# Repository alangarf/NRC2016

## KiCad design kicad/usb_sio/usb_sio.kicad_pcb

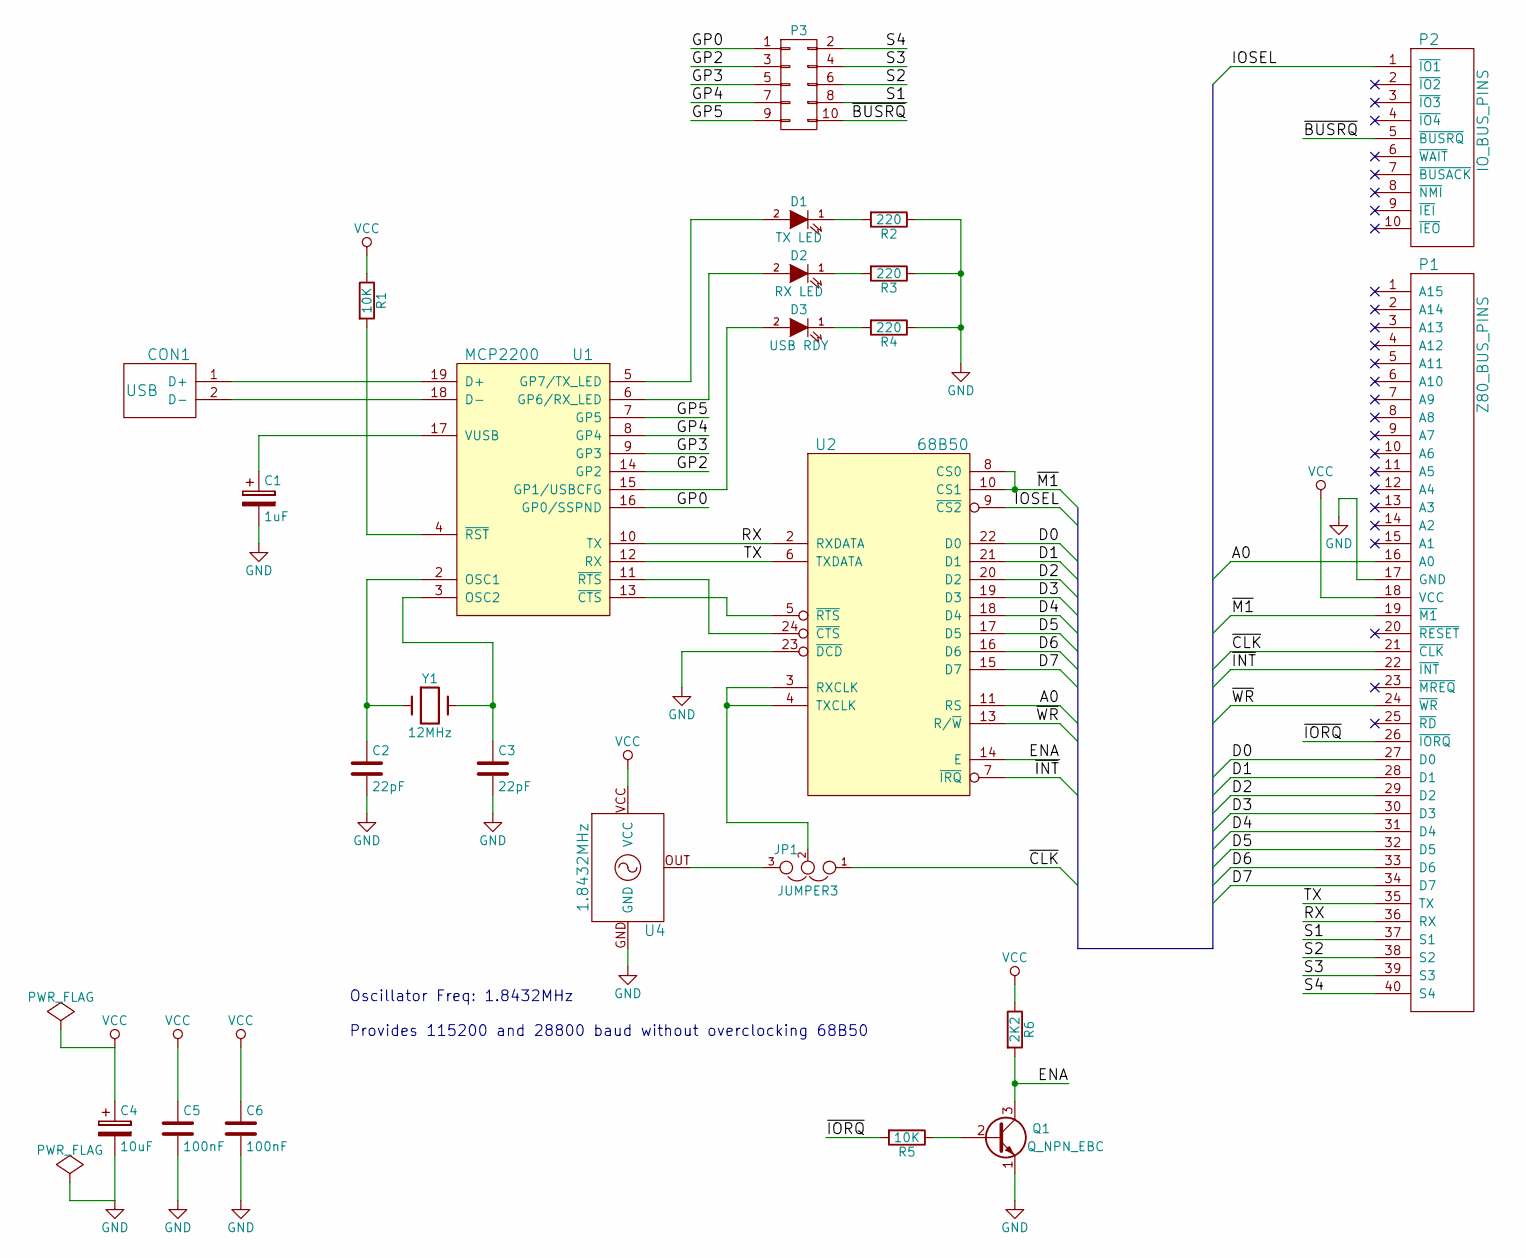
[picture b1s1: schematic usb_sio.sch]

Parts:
C1: 1uF; C_Radial_D5_L6_P2.5
C2, C3: 22pF; C_Disc_D3_P2.5
C4: 10uF; C_Radial_D6.3_L11.2_P2.5
C5, C6: 100nF; C_Disc_D3_P2.5
CON1: USB; Pin_Header_Angled_1x02_nrc2016
D1: TX LED; LED-5MM
D2: RX LED; LED-5MM
D3: USB RDY; LED-5MM
JP1: JUMPER3; Pin_Header_Straight_1x03
P1: Z80_BUS_PINS; Pin_Header_Angled_1x40_nrc2016
P2: IO_BUS_PINS; Pin_Header_Angled_1x10_nrc2016
P3: CONN_02X05; Pin_Header_Straight_2x05
Q1: Q_NPN_EBC; TO-92_Molded_Narrow
R1, R5: 10K; Resistor_Horizontal_RM10mm
R2, R3, R4: 220; Resistor_Horizontal_RM10mm
R6: 2K2; Resistor_Horizontal_RM10mm
U1: MCP2200; SOIC-20W_7.5x12.8mm_Pitch1.27mm
U2: 68B50; DIP-24_W15.24mm_LongPads
U4: 1.8432MHz; OSC_MULTIPACKAGE_DIP
Y1: 12MHz; Crystal_HC49-U_Vertical

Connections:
/A0: P1.16 (A0), U2.11 (RS)
/D0: P1.27 (D0), U2.22 (D0)
/D1: P1.28 (D1), U2.21 (D1)
/D2: P1.29 (D2), U2.20 (D2)
/D3: P1.30 (D3), U2.19 (D3)
/D4: P1.31 (D4), U2.18 (D4)
/D5: P1.32 (D5), U2.17 (D5)
/D6: P1.33 (D6), U2.16 (D6)
/D7: P1.34 (D7), U2.15 (D7)
/ENA: Q1.3 (C), R6.2, U2.14 (E)
/GP0: P3.1, U1.16 (GP0/SSPND)
/GP2: P3.3, U1.14 (GP2)
/GP3: P3.5, U1.9 (GP3)
/GP4: P3.7, U1.8 (GP4)
/GP5: P3.9, U1.7 (GP5)
/RX: P1.36 (RX), U1.10 (TX), U2.2 (RXDATA)
/S1: P1.37 (S1), P3.8
/S2: P1.38 (S2), P3.6
/S3: P1.39 (S3), P3.4
/S4: P1.40 (S4), P3.2
/TX: P1.35 (TX), U1.12 (RX), U2.6 (TXDATA)
/~BUSRQ: P2.5 (~BUSRQ), P3.10
/~CLK: JP1.1, P1.21 (~CLK)
/~INT: P1.22 (~INT), U2.7 (~IRQ)
/~IORQ: P1.26 (~IORQ), R5.2
/~WR: P1.24 (~WR), U2.13 (R/~W)
GND: C1.2, C2.2, C3.2, C4.2, C5.2, C6.2, P1.17 (GND), Q1.1 (E), R2.1, R3.1, R4.1, U1.20 (GND), U2.1 (GND), U2.23 (~DCD), U4.GND
unnamed: C1.1, U1.17 (VUSB)
unnamed: C2.1, U1.2 (OSC1), Y1.1
unnamed: C3.1, U1.3 (OSC2), Y1.2
unnamed: CON1.1 (D+), U1.19 (D+)
unnamed: CON1.2 (D-), U1.18 (D-)
unnamed: D1.1 (K), R2.2
unnamed: D1.2 (A), U1.5 (GP7/TX_LED)
unnamed: D2.1 (K), R3.2
unnamed: D2.2 (A), U1.6 (GP6/RX_LED)
unnamed: D3.1 (K), R4.2
unnamed: D3.2 (A), U1.15 (GP1/USBCFG)
unnamed: JP1.2, U2.3 (RXCLK), U2.4 (TXCLK)
unnamed: JP1.3, U4.OUT
unnamed 40: P2.2 (~IO2); also elsewhere on the board
unnamed 41: P2.3 (~IO3); also elsewhere on the board
unnamed 42: P2.4 (~IO4); also elsewhere on the board
unnamed: Q1.2 (B), R5.1
unnamed: R1.2, U1.4 (~RST)
unnamed: U1.11 (~RTS), U2.24 (~CTS)
unnamed: U1.13 (~CTS), U2.5 (~RTS)

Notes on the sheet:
Oscillator Freq: 1.8432MHz Provides 115200 and 28800 baud without overclocking 68B50

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
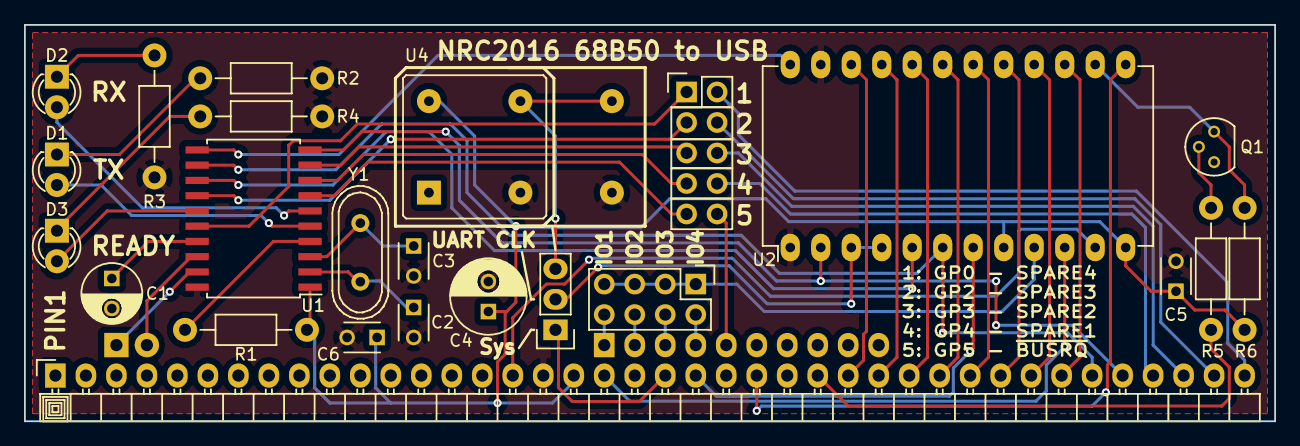
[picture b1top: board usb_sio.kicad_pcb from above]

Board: 2 copper layers, 104.1 x 33.0 mm, 27 parts (0 on the bottom side), 51 nets.

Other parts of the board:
LOGO1: BackLogo; nrc2016_top_logo_1600
P4: CONN_02X04; Pin_Header_Straight_2x04

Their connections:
unnamed 40: P4.6; also elsewhere on the board
unnamed 41: P4.4; also elsewhere on the board
unnamed 42: P4.2; also elsewhere on the board

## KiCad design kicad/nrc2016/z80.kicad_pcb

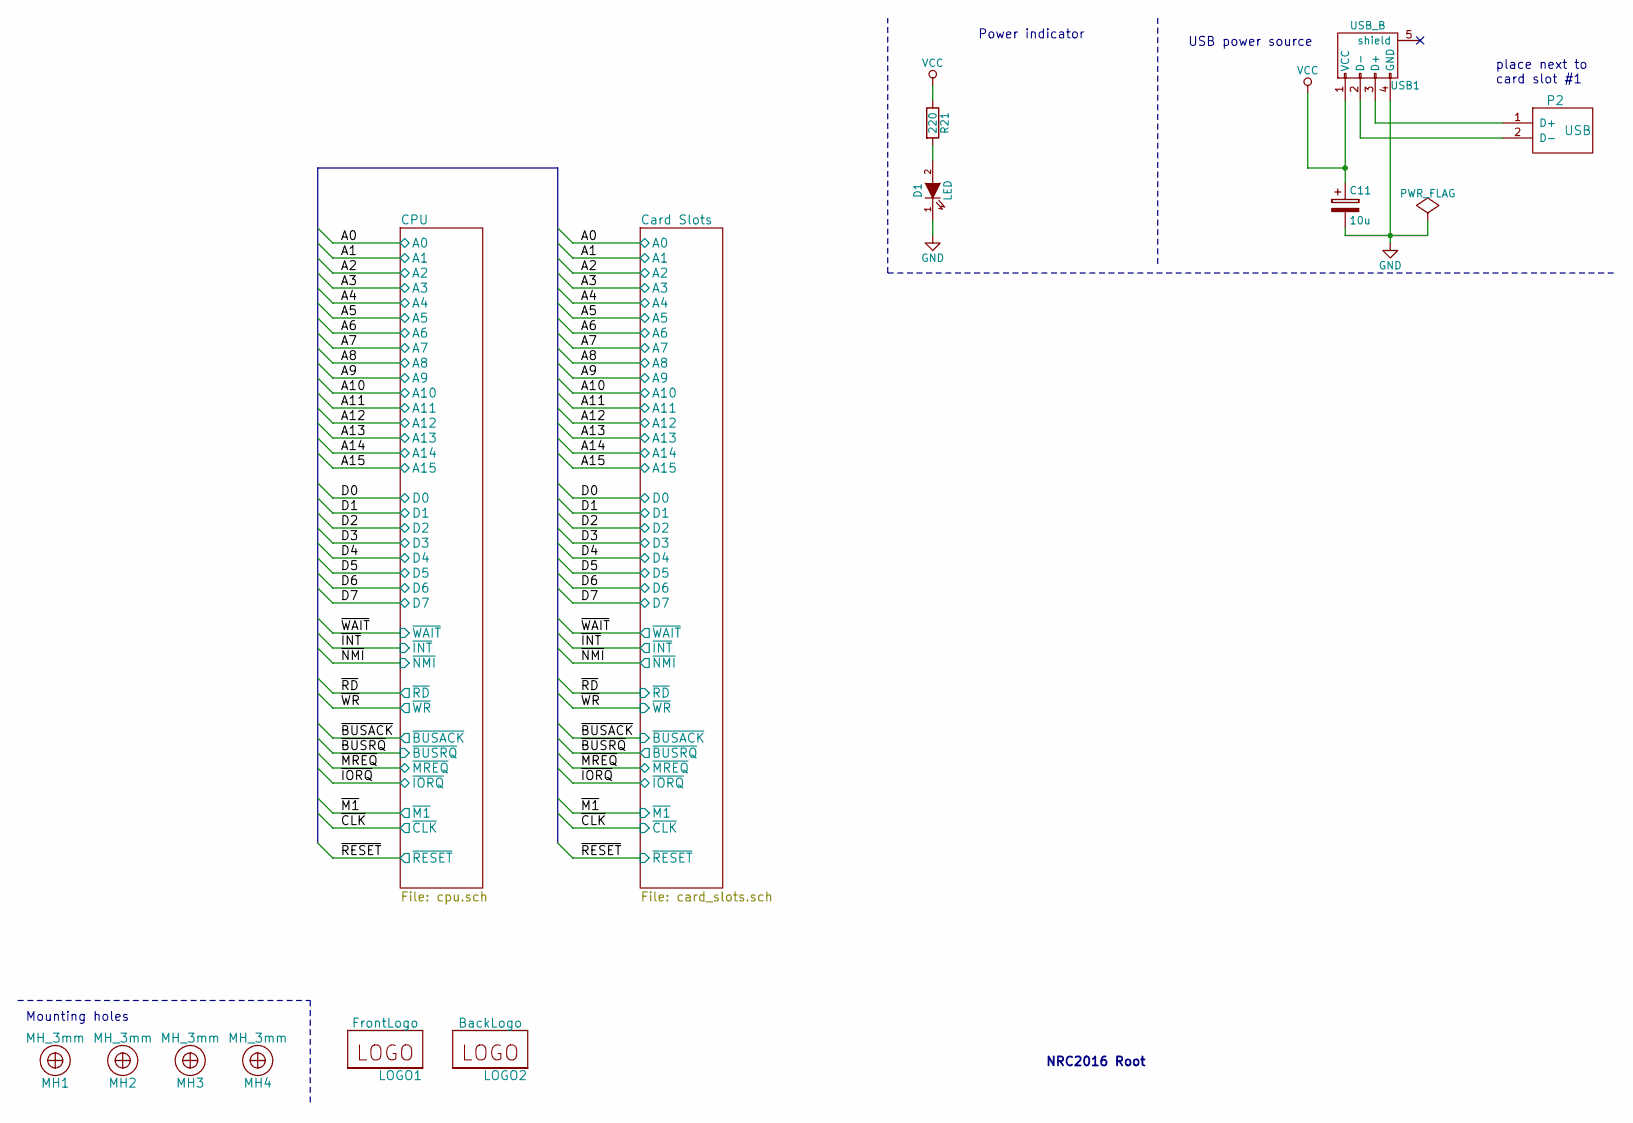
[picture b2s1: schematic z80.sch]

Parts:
C11: 10u; C_Radial_D6.3_L11.2_P2.5
D1: LED; LED-3MM
LOGO1: FrontLogo; nrc2016_top_logo_1600
LOGO2: BackLogo; nrc2016_bottom_logo_600_v2
MH1, MH2, MH3, MH4: MH_3mm; MountingHole_3.2mm_M3
P2: USB; Socket_Strip_Straight_1x02
R21: 220; Resistor_Horizontal_RM7mm
USB1: USB_B

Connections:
GND: C11.2, D1.1 (K), USB1.4 (GND); also elsewhere on the board
unnamed: D1.2 (A), R21.2
unnamed: P2.1 (D+), USB1.3 (D+)
unnamed: P2.2 (D-), USB1.2 (D-)

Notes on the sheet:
NRC2016 Root
Mounting holes
USB power source
Power indicator
place next to card slot #1

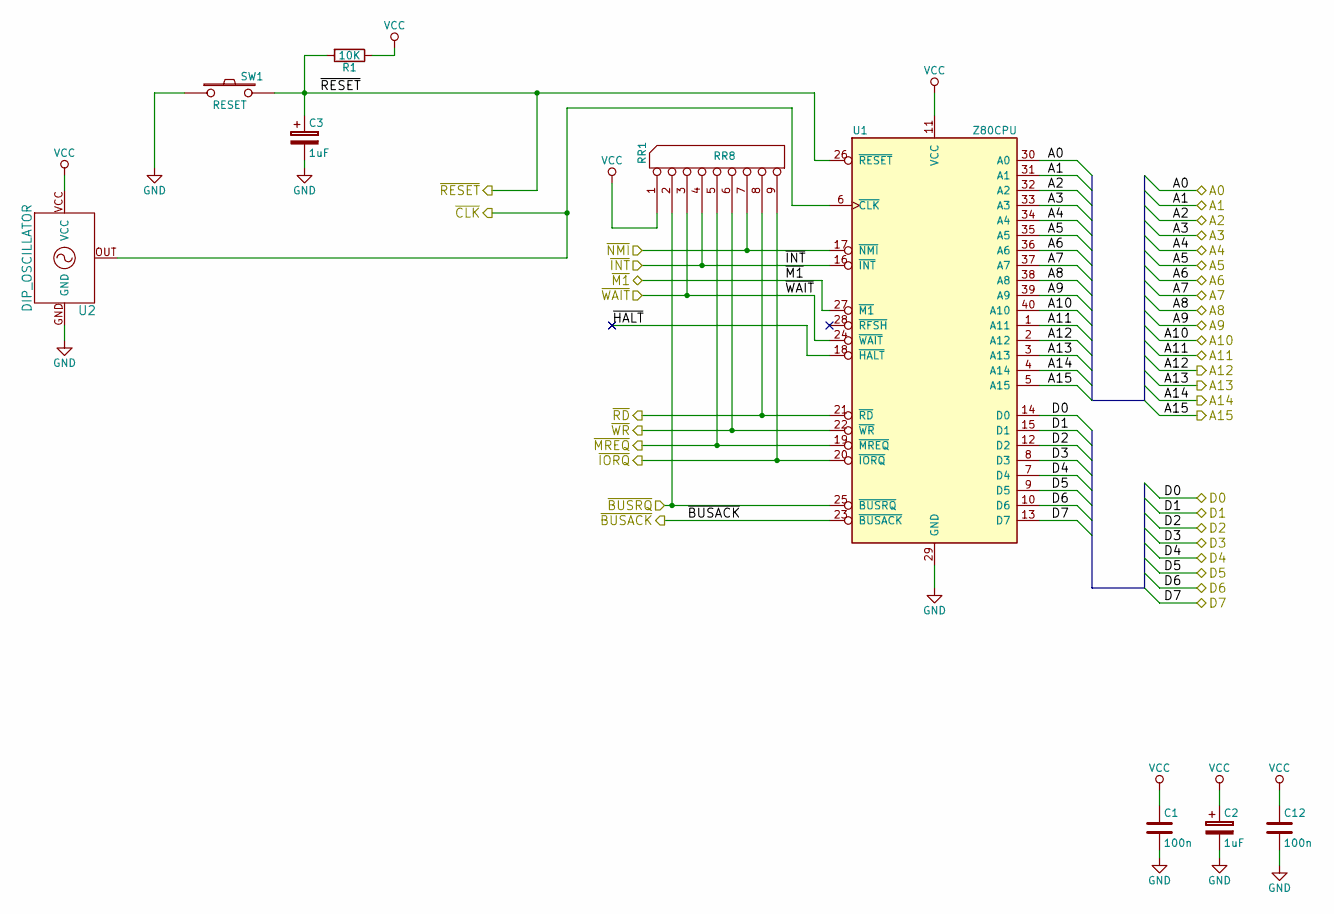
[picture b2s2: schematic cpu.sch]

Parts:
C1, C12: 100n; C_Rect_L4_W2.5_P2.5
C2, C3: 1uF; C_Radial_D5_L6_P2.5
R1: 10K; Resistor_Horizontal_RM7mm
RR1: RR8; Resistor_Array_SIP8
SW1: RESET; SW_PUSH_SMALL
U1: Z80CPU; DIP-40_W15.24mm_LongPads
U2: DIP_OSCILLATOR; OSC_MULTIPACKAGE_DIP

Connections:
/A0: U1.30 (A0); also elsewhere on the board
/A1: U1.31 (A1); also elsewhere on the board
/A2: U1.32 (A2); also elsewhere on the board
/A3: U1.33 (A3); also elsewhere on the board
/A4: U1.34 (A4); also elsewhere on the board
/A5: U1.35 (A5); also elsewhere on the board
/A6: U1.36 (A6); also elsewhere on the board
/A7: U1.37 (A7); also elsewhere on the board
/A8: U1.38 (A8); also elsewhere on the board
/A9: U1.39 (A9); also elsewhere on the board
/A10: U1.40 (A10); also elsewhere on the board
/A11: U1.1 (A11); also elsewhere on the board
/A12: U1.2 (A12); also elsewhere on the board
/A13: U1.3 (A13); also elsewhere on the board
/A14: U1.4 (A14); also elsewhere on the board
/A15: U1.5 (A15); also elsewhere on the board
/D0: U1.14 (D0); also elsewhere on the board
/D1: U1.15 (D1); also elsewhere on the board
/D2: U1.12 (D2); also elsewhere on the board
/D3: U1.8 (D3); also elsewhere on the board
/D4: U1.7 (D4); also elsewhere on the board
/D5: U1.9 (D5); also elsewhere on the board
/D6: U1.10 (D6); also elsewhere on the board
/D7: U1.13 (D7); also elsewhere on the board
/~BUSACK: U1.23 (~BUSACK~); also elsewhere on the board
/~BUSRQ: RR1.2, U1.25 (~BUSRQ~); also elsewhere on the board
/~CLK: U1.6 (~CLK~), U2.OUT; also elsewhere on the board
/~INT: RR1.4, U1.16 (~INT~); also elsewhere on the board
/~IORQ: RR1.9, U1.20 (~IORQ~); also elsewhere on the board
/~M1: U1.27 (~M1~); also elsewhere on the board
/~MREQ: RR1.5, U1.19 (~MREQ~); also elsewhere on the board
/~NMI: RR1.7, U1.17 (~NMI~); also elsewhere on the board
/~RD: RR1.8, U1.21 (~RD~); also elsewhere on the board
/~WAIT: RR1.3, U1.24 (~WAIT~); also elsewhere on the board
/~WR: RR1.6, U1.22 (~WR~); also elsewhere on the board
GND: C1.2, C2.2, C3.2, C12.2, SW1.1, U1.29 (GND), U2.GND; also elsewhere on the board

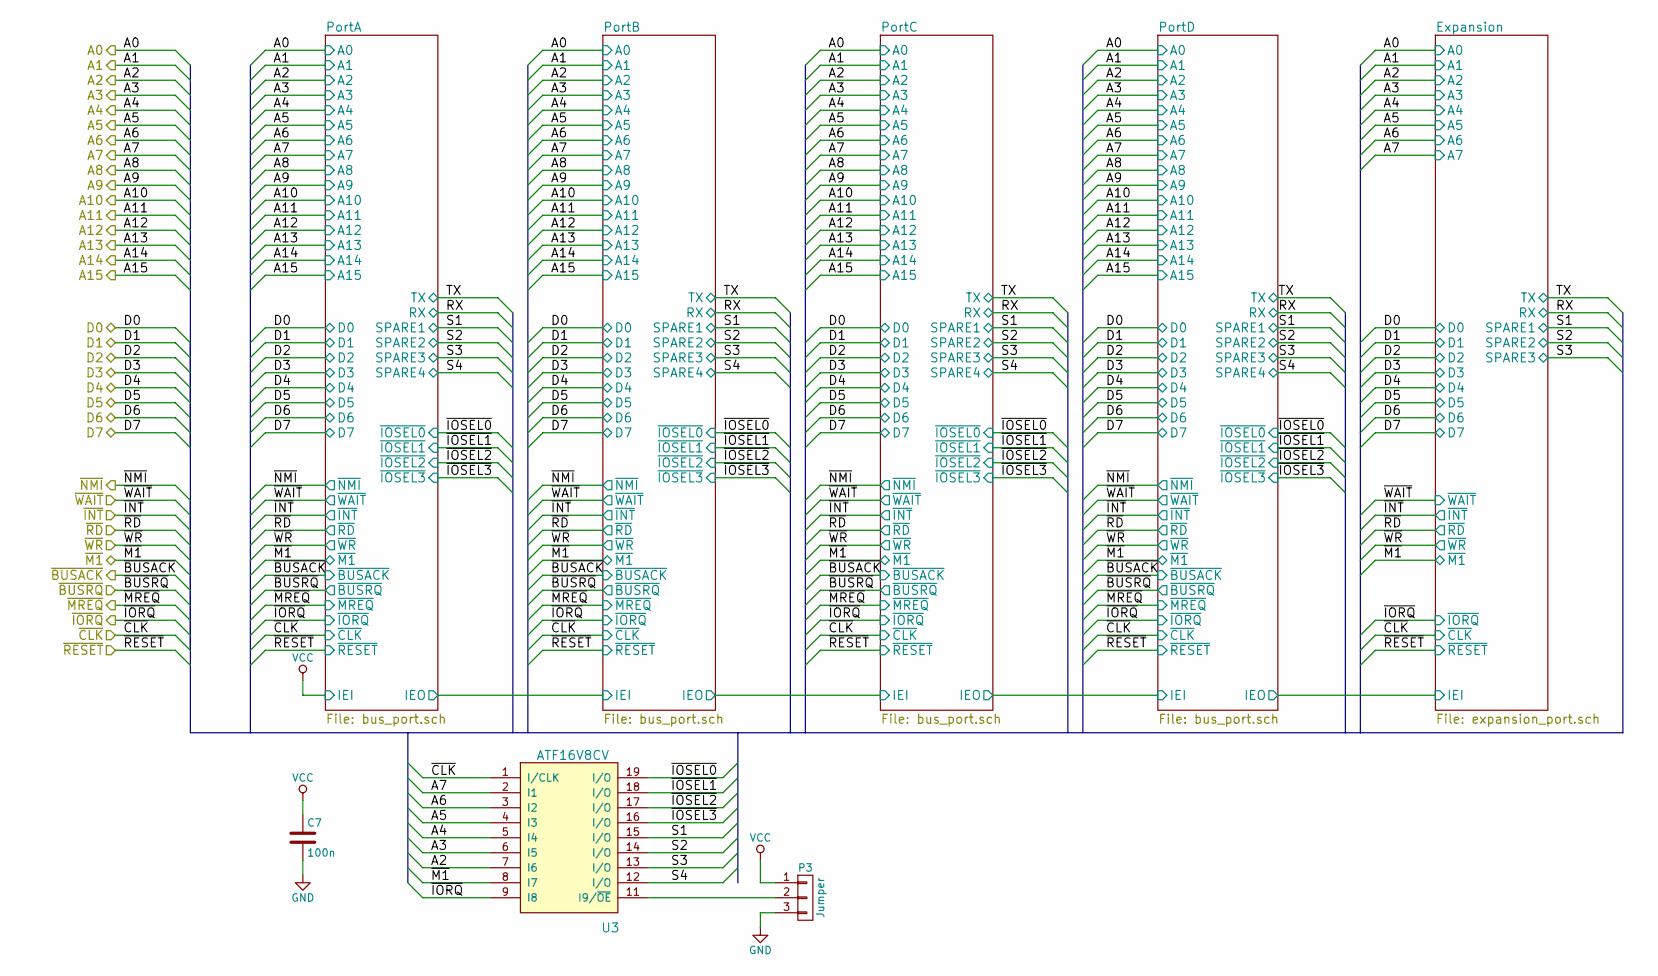
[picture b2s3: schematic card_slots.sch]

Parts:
C7: 100n; C_Rect_L4_W2.5_P2.5
P3: Jumper; Pin_Header_Straight_1x03
U3: ATF16V8CV; DIP-20_W7.62mm_LongPads

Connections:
/A2: U3.7 (I6); also elsewhere on the board
/A3: U3.6 (I5); also elsewhere on the board
/A4: U3.5 (I4); also elsewhere on the board
/A5: U3.4 (I3); also elsewhere on the board
/A6: U3.3 (I2); also elsewhere on the board
/A7: U3.2 (I1); also elsewhere on the board
/Card Slots/S1: U3.15 (I/O); also elsewhere on the board
/Card Slots/S2: U3.14 (I/O); also elsewhere on the board
/Card Slots/S3: U3.13 (I/O); also elsewhere on the board
/Card Slots/S4: U3.12 (I/O); also elsewhere on the board
/Card Slots/~IOSEL0: U3.19 (I/O); also elsewhere on the board
/Card Slots/~IOSEL1: U3.18 (I/O); also elsewhere on the board
/Card Slots/~IOSEL2: U3.17 (I/O); also elsewhere on the board
/Card Slots/~IOSEL3: U3.16 (I/O); also elsewhere on the board
/~CLK: U3.1 (I/CLK); also elsewhere on the board
/~IORQ: U3.9 (I8); also elsewhere on the board
/~M1: U3.8 (I7); also elsewhere on the board
GND: C7.2, P3.3, U3.10 (GND); also elsewhere on the board
unnamed: P3.2, U3.11 (I9/~OE)

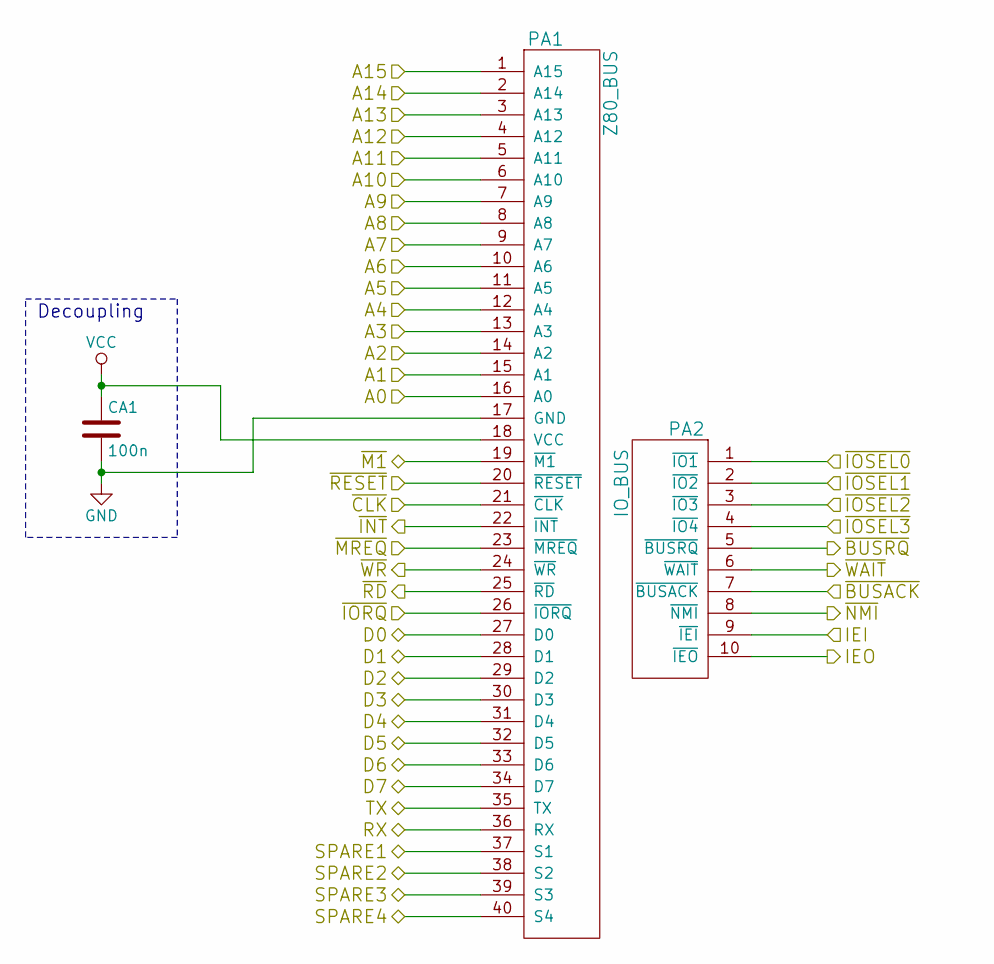
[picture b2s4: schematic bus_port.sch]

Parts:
CA1: 100n; C_Rect_L4_W2.5_P2.5
PA1: Z80_BUS; Socket_Strip_Straight_1x40
PA2: IO_BUS; Socket_Strip_Straight_1x10_NRC2016

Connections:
/A0: PA1.16 (A0); also elsewhere on the board
/A1: PA1.15 (A1); also elsewhere on the board
/A2: PA1.14 (A2); also elsewhere on the board
/A3: PA1.13 (A3); also elsewhere on the board
/A4: PA1.12 (A4); also elsewhere on the board
/A5: PA1.11 (A5); also elsewhere on the board
/A6: PA1.10 (A6); also elsewhere on the board
/A7: PA1.9 (A7); also elsewhere on the board
/A8: PA1.8 (A8); also elsewhere on the board
/A9: PA1.7 (A9); also elsewhere on the board
/A10: PA1.6 (A10); also elsewhere on the board
/A11: PA1.5 (A11); also elsewhere on the board
/A12: PA1.4 (A12); also elsewhere on the board
/A13: PA1.3 (A13); also elsewhere on the board
/A14: PA1.2 (A14); also elsewhere on the board
/A15: PA1.1 (A15); also elsewhere on the board
/Card Slots/PortB/IEI: PA2.10 (~IEO); also elsewhere on the board
/Card Slots/RX: PA1.36 (RX); also elsewhere on the board
/Card Slots/S1: PA1.37 (S1); also elsewhere on the board
/Card Slots/S2: PA1.38 (S2); also elsewhere on the board
/Card Slots/S3: PA1.39 (S3); also elsewhere on the board
/Card Slots/S4: PA1.40 (S4); also elsewhere on the board
/Card Slots/TX: PA1.35 (TX); also elsewhere on the board
/Card Slots/~IOSEL0: PA2.1 (~IO1); also elsewhere on the board
/Card Slots/~IOSEL1: PA2.2 (~IO2); also elsewhere on the board
/Card Slots/~IOSEL2: PA2.3 (~IO3); also elsewhere on the board
/Card Slots/~IOSEL3: PA2.4 (~IO4); also elsewhere on the board
/D0: PA1.27 (D0); also elsewhere on the board
/D1: PA1.28 (D1); also elsewhere on the board
/D2: PA1.29 (D2); also elsewhere on the board
/D3: PA1.30 (D3); also elsewhere on the board
/D4: PA1.31 (D4); also elsewhere on the board
/D5: PA1.32 (D5); also elsewhere on the board
/D6: PA1.33 (D6); also elsewhere on the board
/D7: PA1.34 (D7); also elsewhere on the board
/~BUSACK: PA2.7 (~BUSACK); also elsewhere on the board
/~BUSRQ: PA2.5 (~BUSRQ); also elsewhere on the board
/~CLK: PA1.21 (~CLK); also elsewhere on the board
/~INT: PA1.22 (~INT); also elsewhere on the board
/~IORQ: PA1.26 (~IORQ); also elsewhere on the board
/~M1: PA1.19 (~M1); also elsewhere on the board
/~MREQ: PA1.23 (~MREQ); also elsewhere on the board
/~NMI: PA2.8 (~NMI); also elsewhere on the board
/~RD: PA1.25 (~RD); also elsewhere on the board
/~WAIT: PA2.6 (~WAIT); also elsewhere on the board
/~WR: PA1.24 (~WR); also elsewhere on the board
GND: CA1.2, PA1.17 (GND); also elsewhere on the board

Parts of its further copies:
CB1, CB2: 100n; C_Rect_L4_W2.5_P2.5
CC1: 100n; C_Rect_L4_W2.5_P2.5
CD1: 100n; C_Rect_L4_W2.5_P2.5
PB1: Z80_BUS; Socket_Strip_Straight_1x40
PB2: IO_BUS; Socket_Strip_Straight_1x10_NRC2016
PC1: Z80_BUS; Socket_Strip_Straight_1x40
PC2: IO_BUS; Socket_Strip_Straight_1x10_NRC2016
PD1: Z80_BUS; Socket_Strip_Straight_1x40
PD2: IO_BUS; Socket_Strip_Straight_1x10_NRC2016

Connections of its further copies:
/A0: PB1.16 (A0), PC1.16 (A0), PD1.16 (A0); also elsewhere on the board
/A1: PB1.15 (A1), PC1.15 (A1), PD1.15 (A1); also elsewhere on the board
/A2: PB1.14 (A2), PC1.14 (A2), PD1.14 (A2); also elsewhere on the board
/A3: PB1.13 (A3), PC1.13 (A3), PD1.13 (A3); also elsewhere on the board
/A4: PB1.12 (A4), PC1.12 (A4), PD1.12 (A4); also elsewhere on the board
/A5: PB1.11 (A5), PC1.11 (A5), PD1.11 (A5); also elsewhere on the board
/A6: PB1.10 (A6), PC1.10 (A6), PD1.10 (A6); also elsewhere on the board
/A7: PB1.9 (A7), PC1.9 (A7), PD1.9 (A7); also elsewhere on the board
/A8: PB1.8 (A8), PC1.8 (A8), PD1.8 (A8); also elsewhere on the board
/A9: PB1.7 (A9), PC1.7 (A9), PD1.7 (A9); also elsewhere on the board
/A10: PB1.6 (A10), PC1.6 (A10), PD1.6 (A10); also elsewhere on the board
/A11: PB1.5 (A11), PC1.5 (A11), PD1.5 (A11); also elsewhere on the board
/A12: PB1.4 (A12), PC1.4 (A12), PD1.4 (A12); also elsewhere on the board
/A13: PB1.3 (A13), PC1.3 (A13), PD1.3 (A13); also elsewhere on the board
/A14: PB1.2 (A14), PC1.2 (A14), PD1.2 (A14); also elsewhere on the board
/A15: PB1.1 (A15), PC1.1 (A15), PD1.1 (A15); also elsewhere on the board
/Card Slots/Expansion/IEI: PD2.10 (~IEO); also elsewhere on the board
/Card Slots/PortB/IEI: PB2.9 (~IEI); also elsewhere on the board
/Card Slots/PortC/IEI: PB2.10 (~IEO), PC2.9 (~IEI)
/Card Slots/PortD/IEI: PC2.10 (~IEO), PD2.9 (~IEI)
/Card Slots/RX: PB1.36 (RX), PC1.36 (RX), PD1.36 (RX); also elsewhere on the board
/Card Slots/S1: PB1.37 (S1), PC1.37 (S1), PD1.37 (S1); also elsewhere on the board
/Card Slots/S2: PB1.38 (S2), PC1.38 (S2), PD1.38 (S2); also elsewhere on the board
/Card Slots/S3: PB1.39 (S3), PC1.39 (S3), PD1.39 (S3); also elsewhere on the board
/Card Slots/S4: PB1.40 (S4), PC1.40 (S4), PD1.40 (S4); also elsewhere on the board
/Card Slots/TX: PB1.35 (TX), PC1.35 (TX), PD1.35 (TX); also elsewhere on the board
/Card Slots/~IOSEL0: PB2.1 (~IO1), PC2.1 (~IO1), PD2.1 (~IO1); also elsewhere on the board
/Card Slots/~IOSEL1: PB2.2 (~IO2), PC2.2 (~IO2), PD2.2 (~IO2); also elsewhere on the board
/Card Slots/~IOSEL2: PB2.3 (~IO3), PC2.3 (~IO3), PD2.3 (~IO3); also elsewhere on the board
/Card Slots/~IOSEL3: PB2.4 (~IO4), PC2.4 (~IO4), PD2.4 (~IO4); also elsewhere on the board
/D0: PB1.27 (D0), PC1.27 (D0), PD1.27 (D0); also elsewhere on the board
/D1: PB1.28 (D1), PC1.28 (D1), PD1.28 (D1); also elsewhere on the board
/D2: PB1.29 (D2), PC1.29 (D2), PD1.29 (D2); also elsewhere on the board
/D3: PB1.30 (D3), PC1.30 (D3), PD1.30 (D3); also elsewhere on the board
/D4: PB1.31 (D4), PC1.31 (D4), PD1.31 (D4); also elsewhere on the board
/D5: PB1.32 (D5), PC1.32 (D5), PD1.32 (D5); also elsewhere on the board
/D6: PB1.33 (D6), PC1.33 (D6), PD1.33 (D6); also elsewhere on the board
/D7: PB1.34 (D7), PC1.34 (D7), PD1.34 (D7); also elsewhere on the board
/~BUSACK: PB2.7 (~BUSACK), PC2.7 (~BUSACK), PD2.7 (~BUSACK); also elsewhere on the board
/~BUSRQ: PB2.5 (~BUSRQ), PC2.5 (~BUSRQ), PD2.5 (~BUSRQ); also elsewhere on the board
/~CLK: PB1.21 (~CLK), PC1.21 (~CLK), PD1.21 (~CLK); also elsewhere on the board
/~INT: PB1.22 (~INT), PC1.22 (~INT), PD1.22 (~INT); also elsewhere on the board
/~IORQ: PB1.26 (~IORQ), PC1.26 (~IORQ), PD1.26 (~IORQ); also elsewhere on the board
/~M1: PB1.19 (~M1), PC1.19 (~M1), PD1.19 (~M1); also elsewhere on the board
/~MREQ: PB1.23 (~MREQ), PC1.23 (~MREQ), PD1.23 (~MREQ); also elsewhere on the board
/~NMI: PB2.8 (~NMI), PC2.8 (~NMI), PD2.8 (~NMI); also elsewhere on the board
/~RD: PB1.25 (~RD), PC1.25 (~RD), PD1.25 (~RD); also elsewhere on the board
/~WAIT: PB2.6 (~WAIT), PC2.6 (~WAIT), PD2.6 (~WAIT); also elsewhere on the board
/~WR: PB1.24 (~WR), PC1.24 (~WR), PD1.24 (~WR); also elsewhere on the board
GND: CB1.2, CC1.2, CD1.2, PB1.17 (GND), PC1.17 (GND), PD1.17 (GND); also elsewhere on the board

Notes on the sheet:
Decoupling

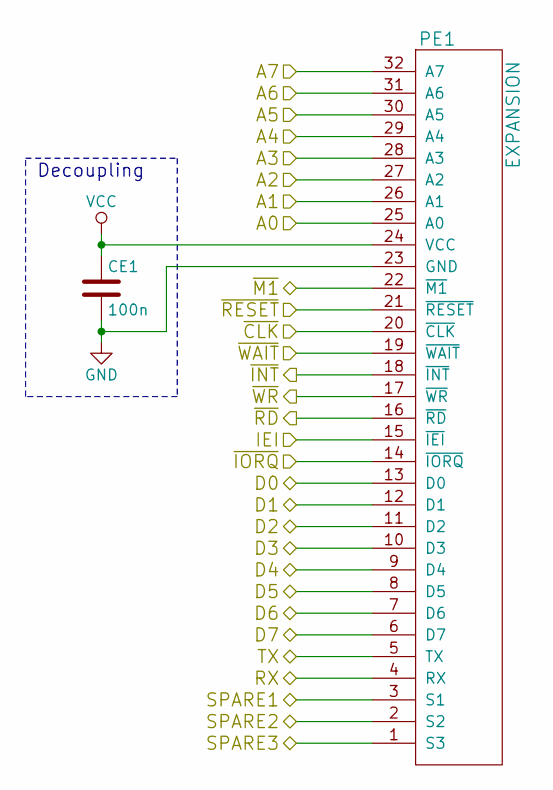
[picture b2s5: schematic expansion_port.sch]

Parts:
CE1: 100n; C_Rect_L4_W2.5_P2.5
PE1: EXPANSION; Socket_Strip_Straight_1x32

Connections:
/A0: PE1.25 (A0); also elsewhere on the board
/A1: PE1.26 (A1); also elsewhere on the board
/A2: PE1.27 (A2); also elsewhere on the board
/A3: PE1.28 (A3); also elsewhere on the board
/A4: PE1.29 (A4); also elsewhere on the board
/A5: PE1.30 (A5); also elsewhere on the board
/A6: PE1.31 (A6); also elsewhere on the board
/A7: PE1.32 (A7); also elsewhere on the board
/Card Slots/Expansion/IEI: PE1.15 (~IEI); also elsewhere on the board
/Card Slots/RX: PE1.4 (RX); also elsewhere on the board
/Card Slots/S1: PE1.3 (S1); also elsewhere on the board
/Card Slots/S2: PE1.2 (S2); also elsewhere on the board
/Card Slots/S3: PE1.1 (S3); also elsewhere on the board
/Card Slots/TX: PE1.5 (TX); also elsewhere on the board
/D0: PE1.13 (D0); also elsewhere on the board
/D1: PE1.12 (D1); also elsewhere on the board
/D2: PE1.11 (D2); also elsewhere on the board
/D3: PE1.10 (D3); also elsewhere on the board
/D4: PE1.9 (D4); also elsewhere on the board
/D5: PE1.8 (D5); also elsewhere on the board
/D6: PE1.7 (D6); also elsewhere on the board
/D7: PE1.6 (D7); also elsewhere on the board
/~CLK: PE1.20 (~CLK); also elsewhere on the board
/~INT: PE1.18 (~INT); also elsewhere on the board
/~IORQ: PE1.14 (~IORQ); also elsewhere on the board
/~M1: PE1.22 (~M1); also elsewhere on the board
/~RD: PE1.16 (~RD); also elsewhere on the board
/~WAIT: PE1.19 (~WAIT); also elsewhere on the board
/~WR: PE1.17 (~WR); also elsewhere on the board
GND: CE1.2, PE1.23 (GND); also elsewhere on the board

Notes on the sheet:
Decoupling

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
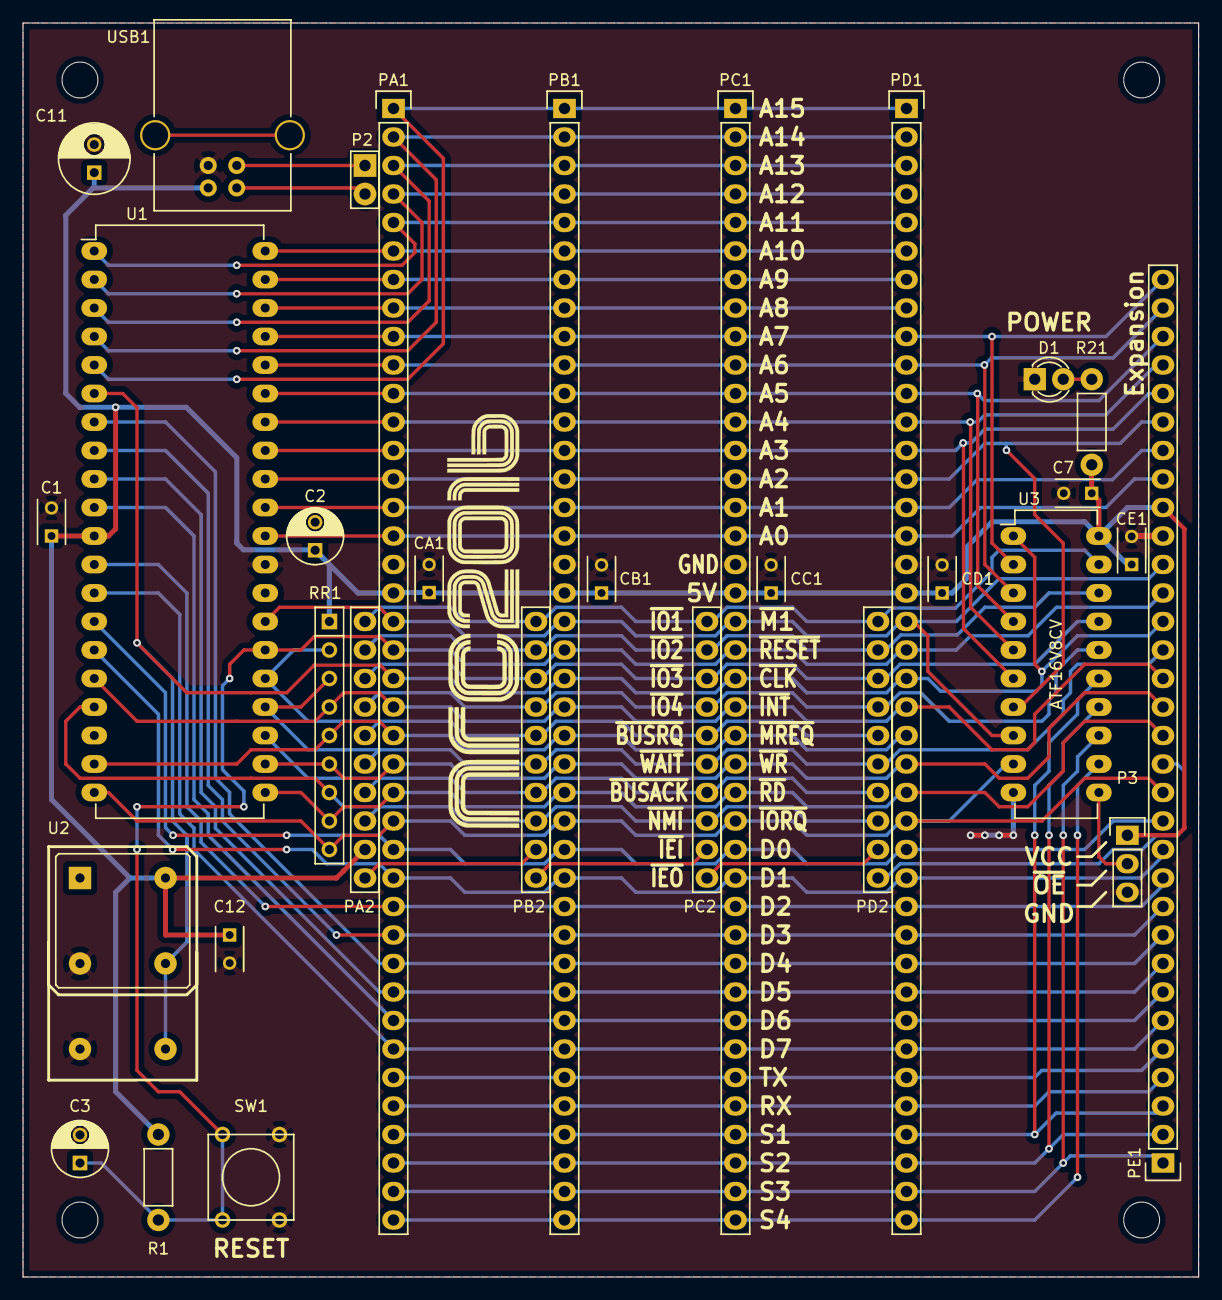
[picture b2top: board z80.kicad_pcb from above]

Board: 2 copper layers, 104.8 x 111.8 mm, 37 parts (0 on the bottom side), 56 nets.

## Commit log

2016-07-03 Added first WIP schema of the new base board with CPU, Clock and APIA onboard
2016-07-04 Added WIP of CPI sheet
2016-07-04 Added kicad source for cpu and root sheet
2016-07-05 Started on bus_port schema
2016-07-08 More WIP added hierarchical sheets for bus
2016-07-08 Added seperate power pin slots to stop inserting cards backwards
2016-07-08 More card slot clean up. Added NMI signal for DMA
2016-07-08 Removed old z80.pdf file
2016-07-08 Added IO sheet, fixed pin types to match z80
2016-07-08 Added IO address decoder, 8 IO slots, partial IO bus buffering. Still to decide: what to do with all the /INT pins? TODO: add bi-directional data bus buffering (2x 74AC241?) for IO boards. This thing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
2016-07-10 Added missing signals to IO and added buffer
    I've removed the /WAIT and also added a somewhat dodgy diode AND to
    handle the bi-directional Dx buffer. Might work, might not.
    Also cleaned up the buses and just tidied things up.
2016-07-10 Added /intack signal and a pri-encoder for /iosel
    Brain fart on the diode crap. Was tired. Added a priority encoder to
    enable the Dx buffer so it properly tristates when no IObus ports are
    selected.
    Added a NOR gate to provide a /intack signal for any board to properly
    detect their interupt has been accepted but the z80. Boards will need to
    figure out who the interupt is for.
2016-07-10 Added interrupt priority pins to bus
    These pins allow the boards to accept an interrupt assert priority of
    the recieved interrupt ACK and load the data bus with a jump offset to
    an ISR. Once a board has assert priority it sets it's IEO low so all
    lower priority boards know the interrupt ACK wasn't for them and to try
    again.
    This will be a beast!
2016-07-10 Removed the interrupt priority circuitry
    After second thought the added complexity just wasn't worth it.
2016-07-20 Added basic board layout WIP
    Switched a few bus lines around to make the layout a little easier.
    Still learning PCBNew, has a few quirks I haven't figured out yet.
2016-07-20 Updated LEDs, added power supply options, added mounting holes in schematic.
2016-07-21 Update PCB, better layout. Got Addr bus back in order
    Think having both USB and DC input would be useful. Switchmode a plus
    then plugpack/battery etc voltage doesn't matter. Plus I have a bag full
    of those parts too!
    I've refdes'd the linear reg just to deal with the net. Will remove if
    we both are happy with switcher. Linear cheaper to kit out I guess.
    Was trying to find a better way to combine USB and DC power rails than
2016-07-21 Just tidied up the addr lines from z80
    Dual layer board, why not use it to space out a bit better. :)
2016-07-21 Added logo 'footprints'
2016-07-21 Added logo to pcb.
2016-07-21 Now for real ..
2016-07-22 PCB layout complete, passes DRC, more tuning required
    One thing not enough buffers for all address lines (missed A5), so
    swapped out the CLK. Not sure if that was a good idea, but didn't want
    to add another chip for a single buffer. :(
2016-07-23 Update with smaller board and through-hole parts.
2016-07-24 Smaller, through hole, done!
    Apart from maybe a few footprint issues and a bit of trace fiddling this
    should be pretty close. Be interesting how much this will cost now. :)
2016-07-24 Change to 7 mils clearance to make cheaper
    7 mils seems to be the minimum clearance for the cheap board houses. So
    reworked the board to match.
2016-07-24 Few more trace tweaks, gave xtal more space.
2016-07-24 ugh another tweak. OCD will kill me.
2016-07-31 New layout complete. Now with rc2014 compat. slots!
    Plus on board address decoding, single stepping using M1 line so button
    is click per instruction. Board is also much smaller!
2016-07-31 Flipped the decoupling caps around for neatness
2016-07-31 Another new board layout. Few tidy ups.
    Removed the single step circuit, not worth the board space and headache.
    Added legend for the IO slot for easy reference. Still toying where to
    put the power LED, annoying me with that resistor. Think I'm happy with
    it now. Spaced things out a little to make it easy for manufacture, made
    sure no traces are near board edges as much as possible.
2016-08-01 Hopefully the final layout
2016-08-01 Can't help myself, damn you OCD!
2016-08-04 * added USB data signals to first slot * added logo to the top of the board. * added logo PNG files.
2016-08-05 Added RAM board schema with GAL
    - Created symbols for 62256 and ATF16V8CV
    - Added start of the RAM board schematic
2016-08-05 Added decoupling caps to RAM board schematic
2016-08-10 * Replaced one card slot with an updated expansion connector. * Replaced '138 with GAL. * Implemented interrupt priority lines IEI/IEO. * Replaced discrete oscillator with 14/8 pin DIP oscillator blo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
2016-08-14 Fixed schema DRC errors
2016-08-14 Added new expansion and GAL to layout.
    Haven't routed the osc. or the reset.
2016-08-14 Updated layout to clean up the power rails
2016-08-14 Noticed missing pin I6 on GAL, added A2 input
2016-08-15 More OCD PCB fiddling, cleaning up traces etc
2016-08-15 Silkscreen tweaking
2016-08-15 Added gitignore to stop all the .bak files driving me nuts
2016-08-15 Removed the RAM board, not much point at the moment.
    Bank switching much more attractive option to rework.
2016-08-15 Removed old IO bus port and hierarchical sheet
2016-08-15 Added symbol for MCP2221A USB to Serial
2016-08-15 Added symbol for Z80_SIO2 device.
    Pins are correct, but their types in KiCad are all wrong. They're all
    currently inputs when they need to reflect the datasheet directions so
    DRC will work. Will fix later
2016-08-15 Added new usb_sio board.
    This board will use a MCP2200 USB controller with hardware flowcontrol
    and a Z80 SIO/2 dual UART.
2016-08-15 More silkscreen tweaks
2016-08-15 Even more silkscreen tweaking
2016-08-16 Added logo schematic elements and new logo for bottom side.
2016-08-16 Dunno what changed. . ?
2016-08-17 * fixed DRC errors on pin 1 of Px2 connectors. * fixed unconnected ground pin issue of GAL. * added 8DIP and 14DIP oscillator block footprint. * updated bottom silkscreen. * added via stitching in a 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
    !! This is NRC016 RC1 !!
2016-08-21 Moved the slot a little further apart.
2016-08-21 updated bottom logo.
2016-08-21 fixed a VCC trace.
2016-08-22 Added WinCUPL files for ATF16V8.
2016-09-03 Fix screw up with VCC and GND on rc2014 slots.
2016-09-09 Moved directory layout around to clean things up
    .. for future work etc.
2016-09-10 Fixed schema paths for libraries of nrc2016
2016-09-10 Fixed up project paths and pcb footprint path moves
2016-09-10 Added MCP2200 USB to serial from microchip
2016-09-10 Update nrc2016 schema and PCB to use new library symbols
    I've added proper schematic symbols for the pre-defined bus sockets to
    stop confusion and error by just using the generic "library" socket
    component and then relying on the net names to define the pins. Screwed
    me once with the VCC and GND switch around, not going to happen again.
2016-09-10 More moving things around. Added sockets and pins symbols
    Makes it easier for DRC and has hints for the right footprints already.
2016-09-10 Added schematic for a nrc2016 USB upgrade board for 68B50
    This could be an upgrade board for owners of an rc2014 and reuse their
    existing 68B50. It uses the IOSEL lines and also puts an appropriate
    oscillator so the 68B50 isn't overclocked to heck.
    Also uses a MCP2200 USB to serial converter that does hardware flow
    control and will have available GPIO for remote I/O using the Microchip
    library (remote reset?).
2016-09-11 Added LEDs and an inverter to the SIO board
2016-09-11 Fixed missing CLK like on SIO board
2016-09-11 WIp on the SIO PCB
2016-09-12 Added major work to SIO board.
    Coming along nicely. Had to use SOIC for the USB to serial converter. :(
2016-09-13 Update to the SIO board, layout complete!
    Added headers for selecting the IOSEL to use, added logo, silkscreen
    legends etc.
2016-09-13 New GAL code for NRC2016, shortened the filename to 8 chars because WinCUPL.
2016-09-13 Added GAL JEDEC file.
2016-09-14 Added prelim schema for a banked RAM and ROM board
    It uses IOSEL for paging in 1 of 4 banks in the lower half of the
    address range.
    BANK0 - ROM
    BANK1 - RAM 32K
    BANK2 - external RAM
    BANK3 - external RAM
2016-09-17 Banked RAM board completed
